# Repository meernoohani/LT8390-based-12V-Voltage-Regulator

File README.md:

# LT8390 Synchronous 4-Switch Buck-Boost Converter (12V Output)

This repository contains the design files for a high-efficiency voltage regulator based on the **LT8390EFE**. The board is designed to provide a stable **12V output** from a wide input voltage range (**13V - 60V**), making it ideal for automotive, industrial, and battery-powered applications where the input voltage can be higher or lower than the desired output.

## 🛠 Features
* **Controller:** Analog Devices (Linear Tech) LT8390.
* **Topology:** Synchronous 4-switch Buck-Boost (provides seamless transitions between modes).
* **Input Voltage Range:** 13V to 60V DC.
* **Output Voltage:** Fixed 12V DC.
* **Efficiency:** High-efficiency synchronous rectification using low $R_{DS(on)}$ MOSFETs.
* **Design Tool:** Created with **KiCad 9.0**.
* **Form Factor:** Compact PCB with optimized thermal management and power paths.

## 🔌 Hardware Highlights
* **Power Stage:** Utilizes four external N-channel MOSFETs for maximum current capability and efficiency.
* **Integrated Protection:** Includes input undervoltage lockout (UVLO) and soft-start functionality.
* **Thermal Design:** Large copper pours and thermal vias are implemented to manage heat dissipation from the inductor and MOSFETs.
* **EMI Optimization:** Provision for spread spectrum frequency modulation (SSFM) to reduce EMI signatures.

## ⚙️ Technical Specifications
| Parameter | Value |
| :--- | :--- |
| **Input Voltage ($V_{IN}$)** | 13V - 60V |
| **Output Voltage ($V_{OUT}$)** | 12V |
| **Switching Frequency** | Set via RT resistor (refer to schematic) |
| **Inductor** | High-current shielded power inductor |
| **Input Capacitance** | High-voltage electrolytic + ceramic decoupling array |

## 🚀 Potential Applications
* **Automotive Power:** Stable 12V rail for electronics from a fluctuating 24V/48V vehicle bus.
* **Battery Regulation:** Maintaining 12V from a discharging high-voltage battery pack (e.g., 10S-14S Li-ion).
* **Industrial Control:** Wide-input 24V/48V DC-DC conversion for sensitive sensors.
* **Solar Power:** Regulation of variable solar panel outputs to a fixed 12V battery charging rail.

---
*Note: This project involves high-current power electronics. Ensure proper cooling and current-limit testing during initial bring-up.*

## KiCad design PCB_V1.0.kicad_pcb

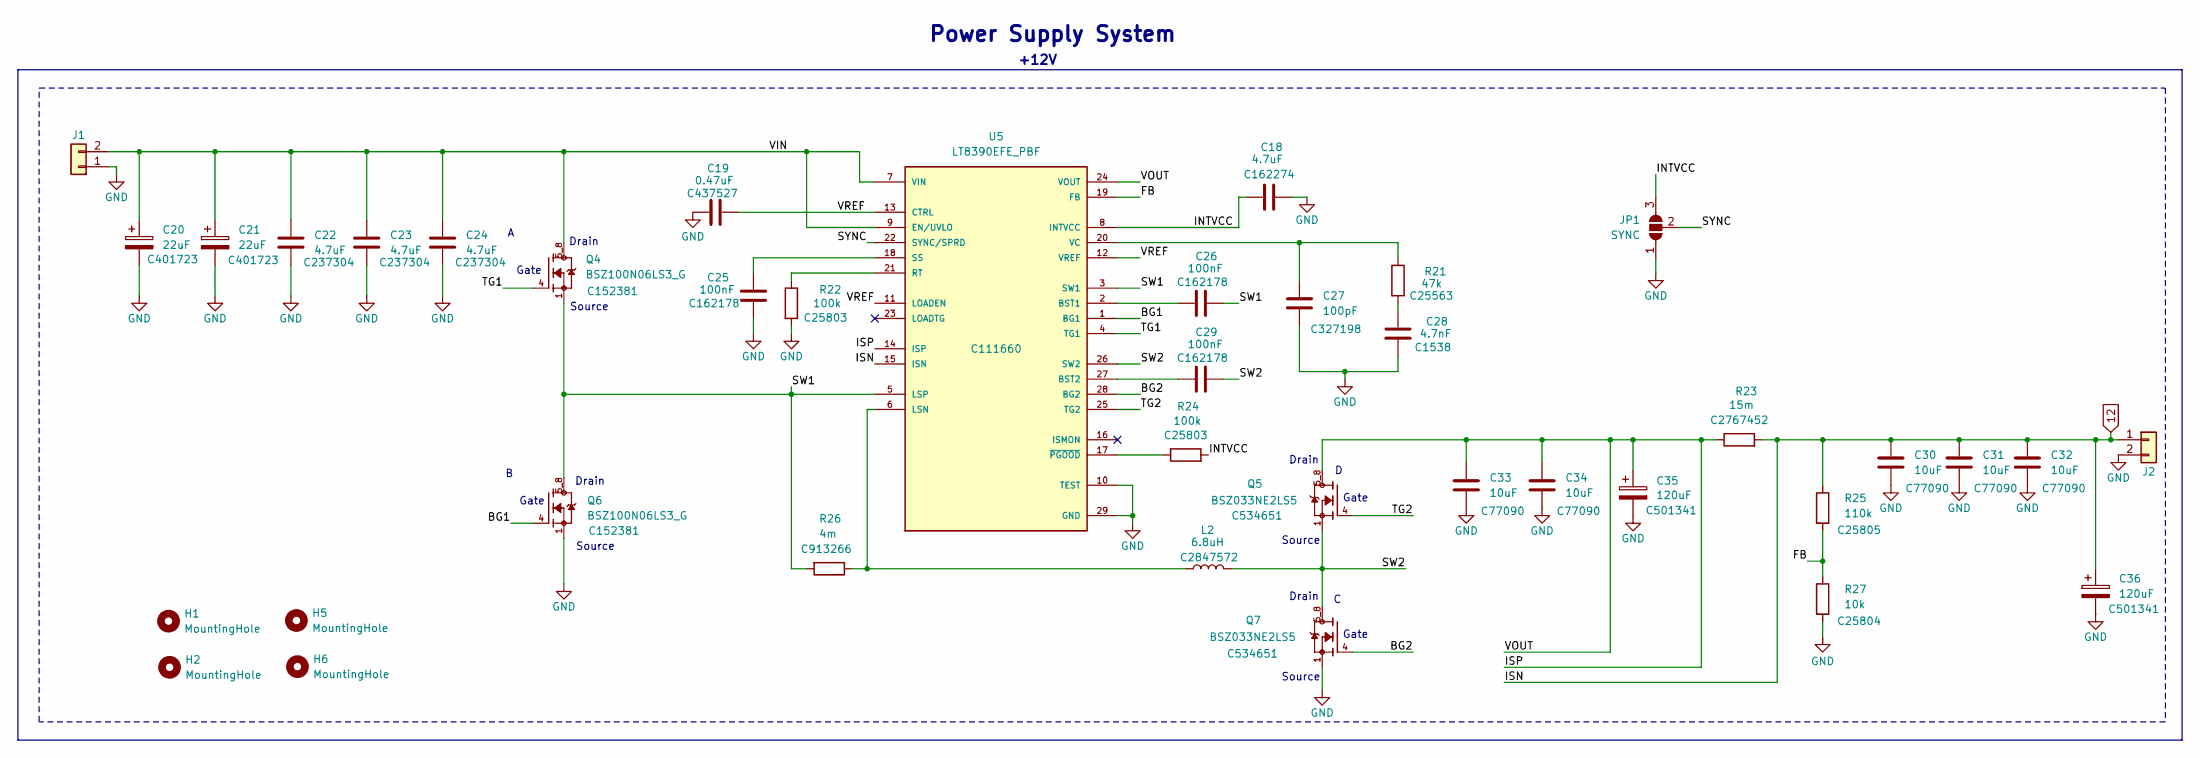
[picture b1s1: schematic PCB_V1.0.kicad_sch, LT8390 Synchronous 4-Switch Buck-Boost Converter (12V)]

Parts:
C18: 4.7uF; C_0603_1608Metric; LCSC C162274
C19: 0.47uF; C_0402_1005Metric; LCSC C437527
C20, C21: 22uF; CP_Elec_8x6.2; LCSC C401723
C22, C23, C24: 4.7uF; C_1206_3216Metric; LCSC C237304
C25, C26, C29: 100nF; C_0402_1005Metric; LCSC C162178
C27: 100pF; C_0402_1005Metric; LCSC C327198
C28: 4.7nF; C_0402_1005Metric; LCSC C1538
C30, C31, C32, C33, C34: 10uF; C_1206_3216Metric; LCSC C77090
C35, C36: 120uF; CP_Elec_10x12.6; LCSC C501341
H1, H2, H5, H6: MountingHole; MountingHole_2.2mm_M2_DIN965_Pad
J1, J2: Conn_01x02; JST_XH_B2B-XH-A_1x02_P2.50mm_Vertical
JP1: SYNC; SolderJumper-3_P2.0mm_Open_TrianglePad1.0x1.5mm
L2: 6.8uH; L_Sunlord_MWSA1265S; LCSC C2847572
Q4, Q6: BSZ100N06LS3_G; TRANS_BSZ100N06LS3_G; PARTREV 2.4; LCSC C152381
Q5, Q7: BSZ033NE2LS5; TRANS_BSZ100N06LS3_G; PARTREV 2.4; LCSC C534651
R21: 47k; C_0402_1005Metric; LCSC C25563
R22, R24: 100k; C_0603_1608Metric; LCSC C25803
R23: 15m; R_0805_2012Metric; LCSC C2767452
R25: 110k; R_0603_1608Metric; LCSC C25805
R26: 4m; R_2512_6332Metric; LCSC C913266
R27: 10k; R_0603_1608Metric; LCSC C25804
U5: LT8390EFE_PBF; PARTREV B; LCSC C111660

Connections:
12: C30.1, C31.1, C32.1, C36.1, J2.1, R23.2, R25.1, U5.15 (ISN)
/BG1: Q6.4, U5.1 (BG1)
/BG2: Q7.4, U5.28 (BG2)
/FB: R25.2, R27.1, U5.19 (FB)
/INTVCC: C18.1, JP1.3 (B), R24.2, U5.8 (INTVCC)
/ISP: C33.1, C34.1, C35.1, Q5.5_8, R23.1, U5.14 (ISP), U5.24 (VOUT)
/SW1: C26.2, Q4.1, Q4.2, Q4.3, Q6.5_8, R26.2, U5.3 (SW1), U5.5 (LSP)
/SW2: C29.2, L2.2, Q5.1, Q5.2, Q5.3, Q7.5_8, U5.26 (SW2)
/SYNC: JP1.2 (C), U5.22 (SYNC/SPRD)
/TG1: Q4.4, U5.4 (TG1)
/TG2: Q5.4, U5.25 (TG2)
/VIN: C20.1, C21.1, C22.1, C23.1, C24.1, J1.2, Q4.5_8, U5.7 (VIN), U5.9 (EN/UVLO)
/VREF: C19.1, U5.11 (LOADEN), U5.12 (VREF), U5.13 (CTRL)
GND: C18.2, C19.2, C20.2, C21.2, C22.2, C23.2, C24.2, C25.1, C27.2, C28.2, C30.2, C31.2, C32.2, C33.2, C34.2, C35.2, C36.2, J1.1, J2.2, JP1.1 (A), Q6.1, Q6.2, Q6.3, Q7.1, Q7.2, Q7.3, R22.2, R27.2, U5.10 (TEST), U5.29 (GND)
unnamed: C28.1, R21.2
unnamed: C26.1, U5.2 (BST1)
unnamed: C29.1, U5.27 (BST2)
unnamed: L2.1, R26.1, U5.6 (LSN)
unnamed: R22.1, U5.21 (RT)
unnamed: C25.2, U5.18 (SS)
unnamed: C27.1, R21.1, U5.20 (VC)
unnamed: R24.1, U5.17 (~PGOOD)

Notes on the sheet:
Gate
Drain
Source
+12V
Power Supply System

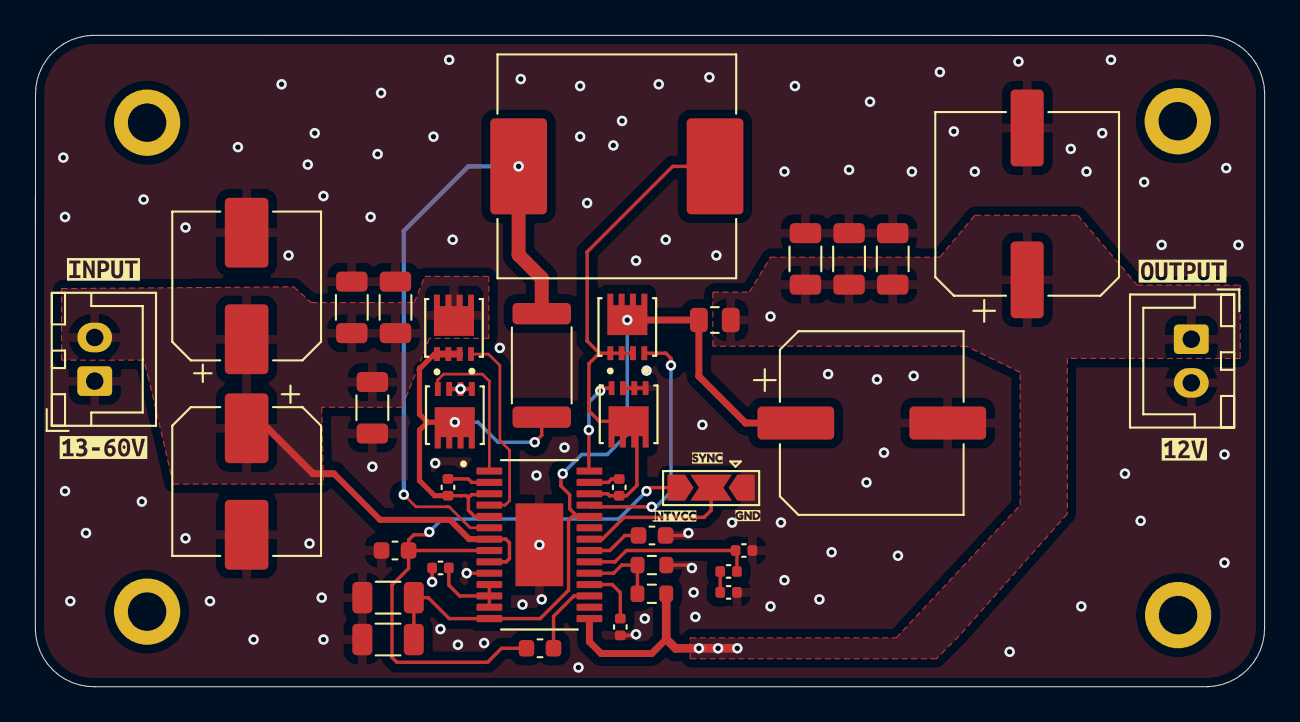
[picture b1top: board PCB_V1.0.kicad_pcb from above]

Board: 2 copper layers, 70.4 x 37.3 mm, 46 parts (0 on the bottom side), 22 nets.

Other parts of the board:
kibuzzard-69945A74: G***; kibuzzard-69945A74
kibuzzard-69945B09: G***; kibuzzard-69945B09
kibuzzard-69945CB2: G***; kibuzzard-69945CB2
kibuzzard-69945CBE: G***; kibuzzard-69945CBE
kibuzzard-69945D5F: G***; kibuzzard-69945D5F
kibuzzard-69945D8C: G***; kibuzzard-69945D8C
kibuzzard-69945DBC: G***; kibuzzard-69945DBC

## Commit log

2026-02-21 init
2026-02-21 Add README for LT8390 Buck-Boost Converter project
    Added detailed information about the LT8390 synchronous buck-boost converter, including features, hardware highlights, technical specifications, and potential applications.
